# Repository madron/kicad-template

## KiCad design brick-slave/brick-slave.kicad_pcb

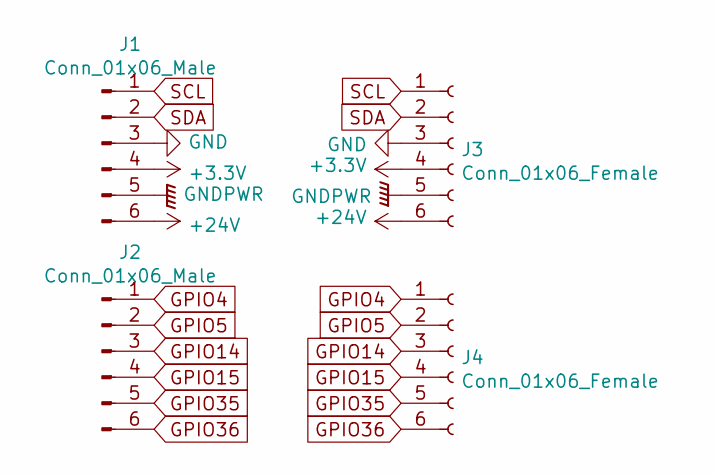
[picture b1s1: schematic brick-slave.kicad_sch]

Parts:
J1, J2: Conn_01x06_Male; PinHeader_1x06_P2.54mm_Horizontal
J3, J4: Conn_01x06_Female; PinSocket_1x06_P2.54mm_Horizontal

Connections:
+3V3: J1.4, J3.4
+5V: J1.6, J3.6
GND: J1.3, J3.3
GNDPWR: J1.5, J3.5
GPIO4: J2.1, J4.1
GPIO5: J2.2, J4.2
GPIO14: J2.3, J4.3
GPIO15: J2.4, J4.4
GPIO35: J2.5, J4.5
GPIO36: J2.6, J4.6
SCL: J1.1, J3.1
SDA: J1.2, J3.2

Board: 2 copper layers, 8 parts (0 on the bottom side), 12 nets, no tracks yet.

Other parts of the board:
H1, H2, H3, H4: MountingHole; MountingHole_3.2mm_M3

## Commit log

2021-01-24 add brick-slave
2021-01-24 move gitignore
2021-05-31 update brick-slave template
2021-07-10 brick-slave - move female connector
2021-07-10 brick-slave - move input connectors
2021-07-17 upgrade format
2021-07-28 update brick-slave
2021-08-01 change PWR voltage
2021-08-02 update nets
2021-08-03 refactor brick-slave
